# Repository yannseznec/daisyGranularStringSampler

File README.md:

## STR-500

This is all of the code and build info for the STR-500 gestural granular synthesizer. 

It is a granular synthesizer built for the Daisy Seed which uses a salvaged Gametrak string controller to playback a recorded sample. 

To-do: 
- develop this Readme
- add an actual to-do list to this Readme

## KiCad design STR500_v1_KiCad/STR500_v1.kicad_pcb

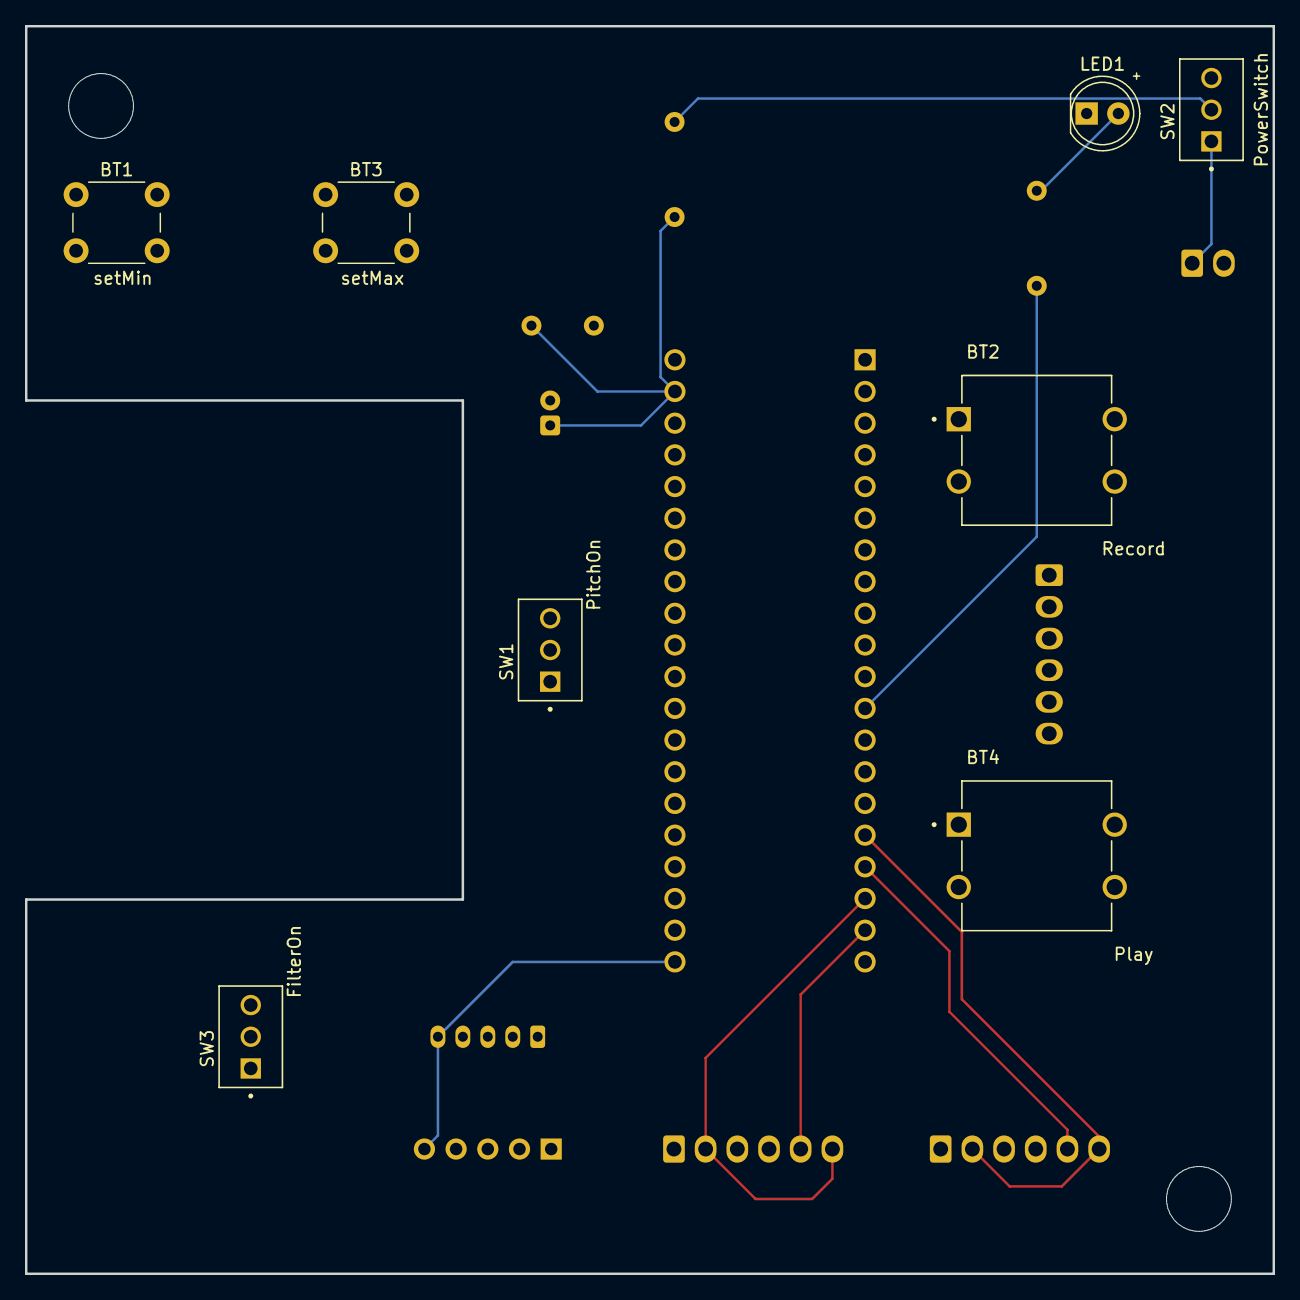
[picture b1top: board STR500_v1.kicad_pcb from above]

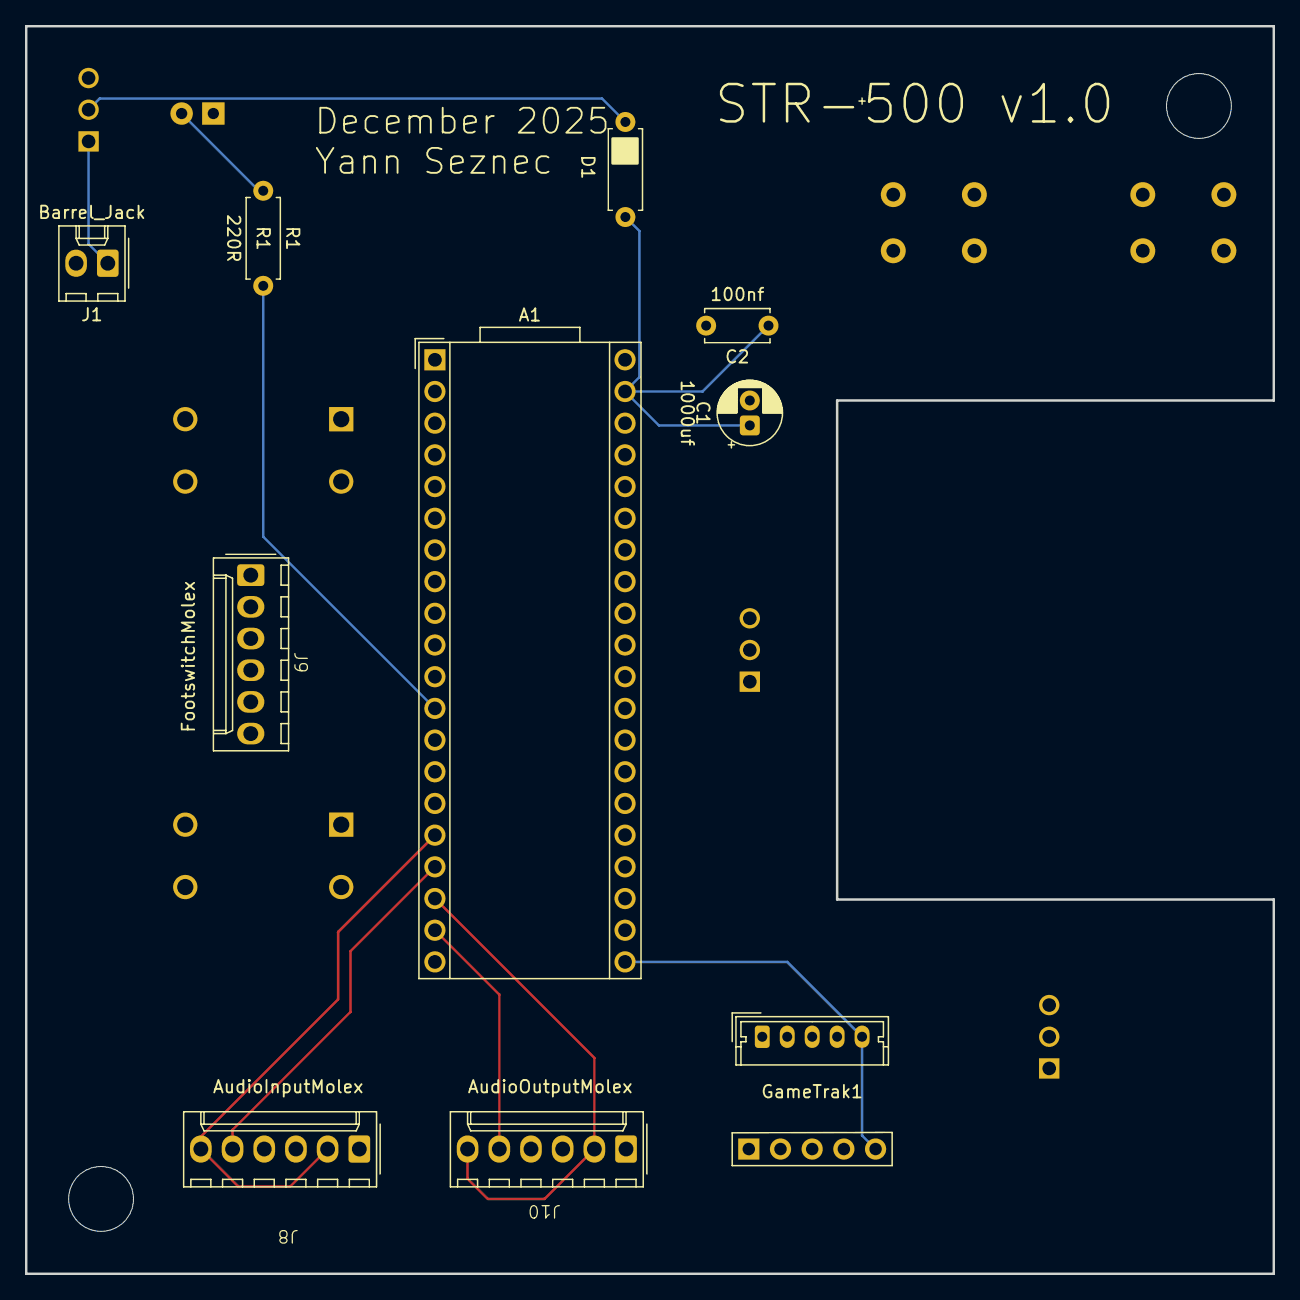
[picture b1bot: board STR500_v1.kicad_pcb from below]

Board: 4 copper layers, 100.0 x 100.0 mm, 18 parts (10 on the bottom side), 22 nets.

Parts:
A1: Electrosmith_Daisy_Seed_Rev4; Electrosmith_Daisy_Seed
BT1: setMin; SW_PUSH_6mm
BT2: Record; SW_TS13-1212-73-BK-160-D
BT3: setMax; SW_PUSH_6mm
BT4: Play; SW_TS13-1212-73-BK-160-D
C1: 1000uf; CP_Radial_D5.0mm_P2.00mm
C2: 100nf; C_Disc_D5.0mm_W2.5mm_P5.00mm
D1: D; R_Axial_DIN0207_L6.3mm_D2.5mm_P7.62mm_Horizontal
GameTrak1: Molex_Micro-Latch_53253-0570_1x05_P2.00mm_Vertical
J1: Barrel_Jack; Molex_KK-254_AE-6410-02A_1x02_P2.54mm_Vertical
J8: AudioInputMolex; Molex_sixpin_twoJacks
J9: FootswitchMolex; Molex_sixpin_twoJacks
J10: AudioOutputMolex; Molex_sixpin_twoJacks
LED1: LED; LED_D5.0mm
R1: 220R; R_Axial_DIN0207_L6.3mm_D2.5mm_P7.62mm_Horizontal
SW1: PitchOn; submini_toggle
SW2: PowerSwitch; submini_toggle
SW3: FilterOn; submini_toggle

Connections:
+3.3V: A1.21 (3V3_A), GameTrak1.5
+5V: A1.39 (VIN), C1.1, C2.1, D1.1 (K)
/BT1: A1.4 (SD_DATA_1), BT1.2 (B)
/BT2: A1.5 (SD_DATA_0), BT3.2 (B)
/BT3: A1.6 (SD_CMD), J9.T1
/BT4: A1.7 (SD_CLK), J9.T2
/LED: A1.12 (I2C1_SCL), R1.2
/Pot0: A1.22 (ADC_0), GameTrak1.2
/Pot1: A1.23 (ADC_1), GameTrak1.3
/Pot2: A1.24 (ADC_2), GameTrak1.4
/Sw1: A1.2 (SD_DATA_3), SW1.2 (B)
/Sw2: A1.3 (SD_DATA_2), SW3.2 (B)
/inL: A1.16 (AUDIO_IN_1), J8.T1, J8.TN2
/inR: A1.17 (AUDIO_IN_2), J8.T2
/outL: A1.18 (AUDIO_OUT_1), J10.T1, J10.TN2
/outR: A1.19 (AUDIO_OUT_2), J10.T2
GND: A1.20 (AGND), A1.40 (DGND), BT1.1 (A), BT2.1 (A), BT3.1 (A), BT4.1 (A), C1.2, C2.2, GameTrak1.1, J1.2, J8.S1, J8.S2, J9.S1, J9.S2, J10.S1, J10.S2, LED1.1 (K), SW1.1 (A), SW3.1 (A)
unnamed: BT2.2 (B), J9.TN1
unnamed: BT4.2 (B), J9.TN2
unnamed: D1.2 (A), SW2.2 (B)
unnamed: LED1.2 (A), R1.1
unnamed: J1.1, SW2.1 (A)

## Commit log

2025-12-08 Create LICENSE
2025-12-19 changes for the PCB version
2025-12-19 added KiCad files
2026-01-20 new KiCAD, small improvements and cleanup to the Pd patches
2026-01-20 cleanup
2026-01-22 cleanup and 3D model/drill files
2026-02-05 remove dsstore
2026-02-09 documentation
2026-04-12 update KiCAD, including first version
